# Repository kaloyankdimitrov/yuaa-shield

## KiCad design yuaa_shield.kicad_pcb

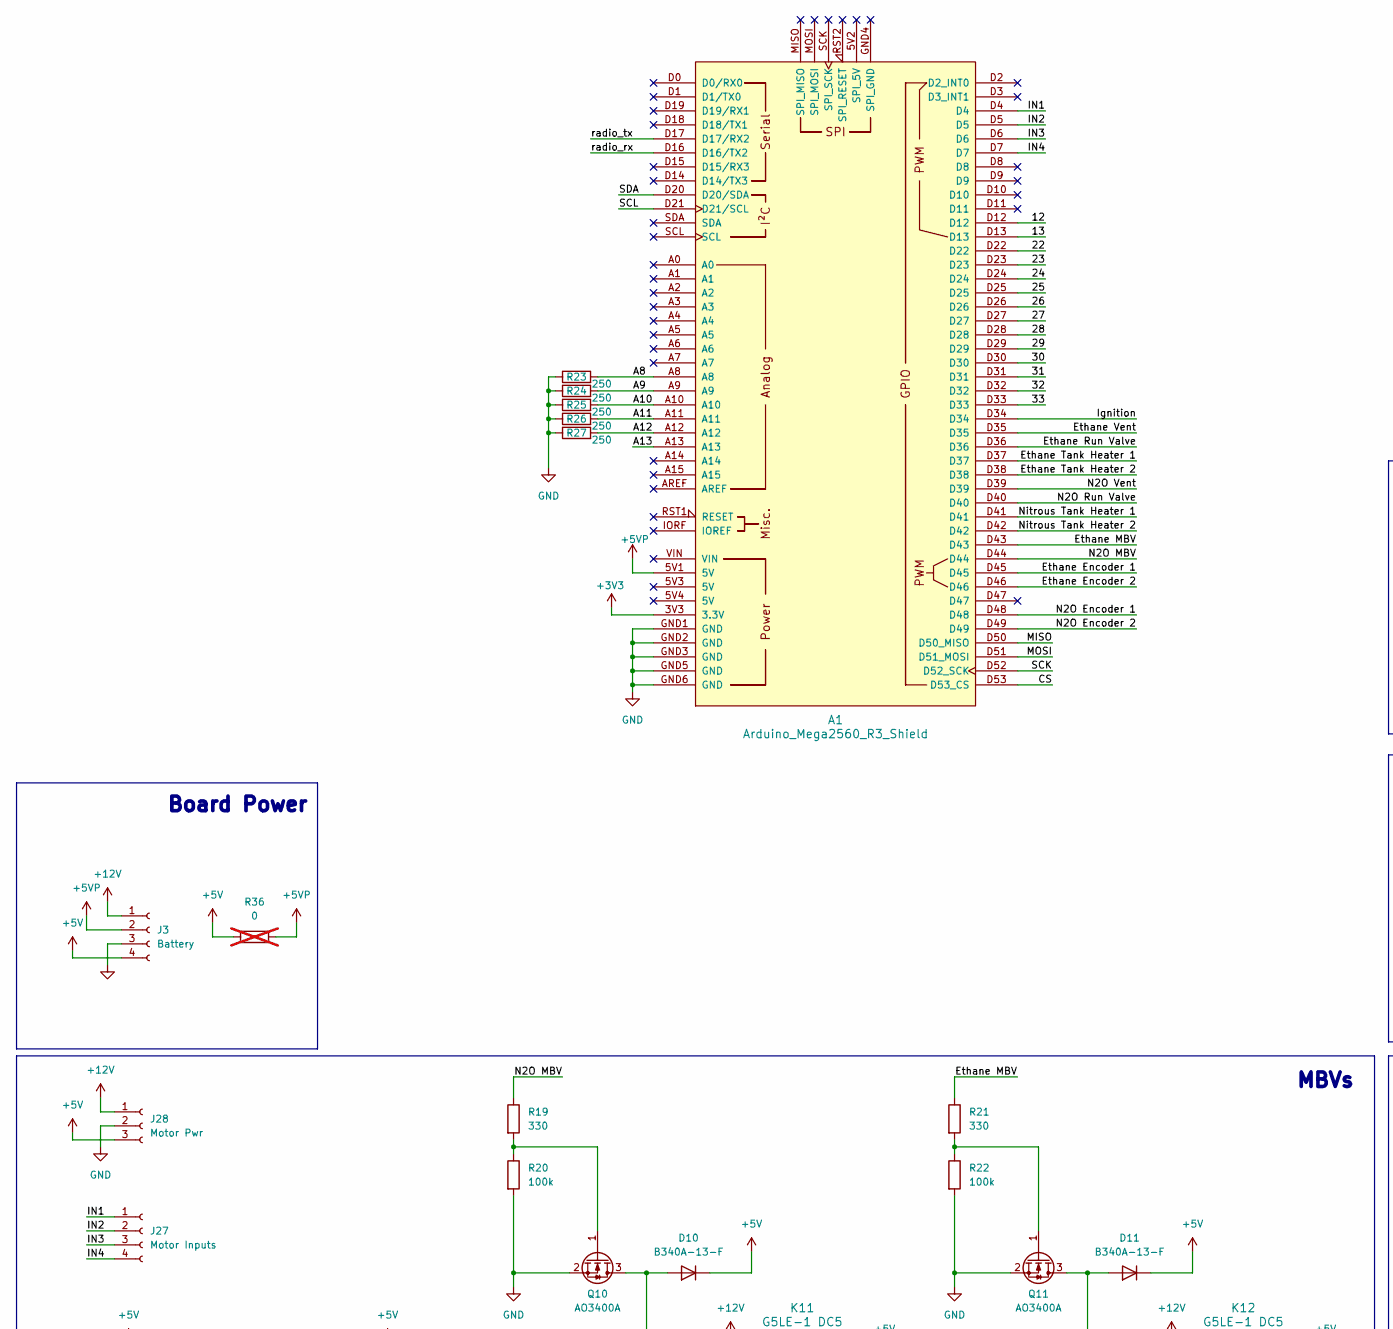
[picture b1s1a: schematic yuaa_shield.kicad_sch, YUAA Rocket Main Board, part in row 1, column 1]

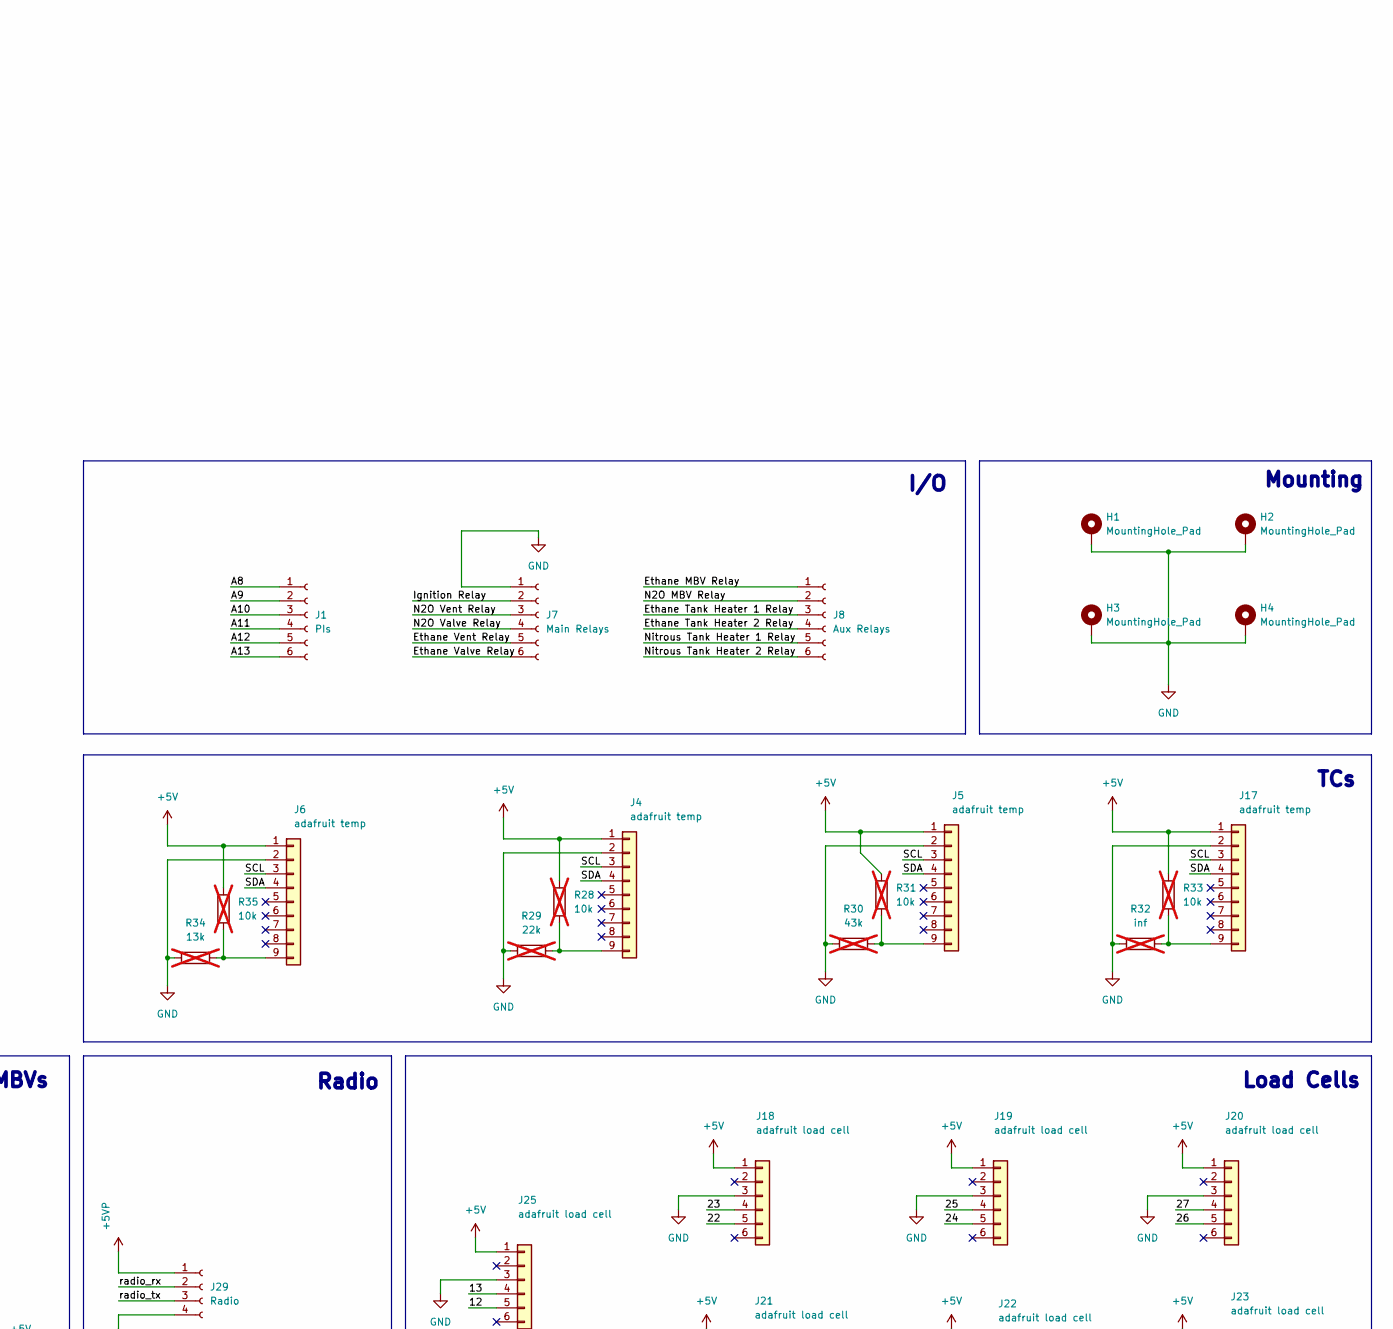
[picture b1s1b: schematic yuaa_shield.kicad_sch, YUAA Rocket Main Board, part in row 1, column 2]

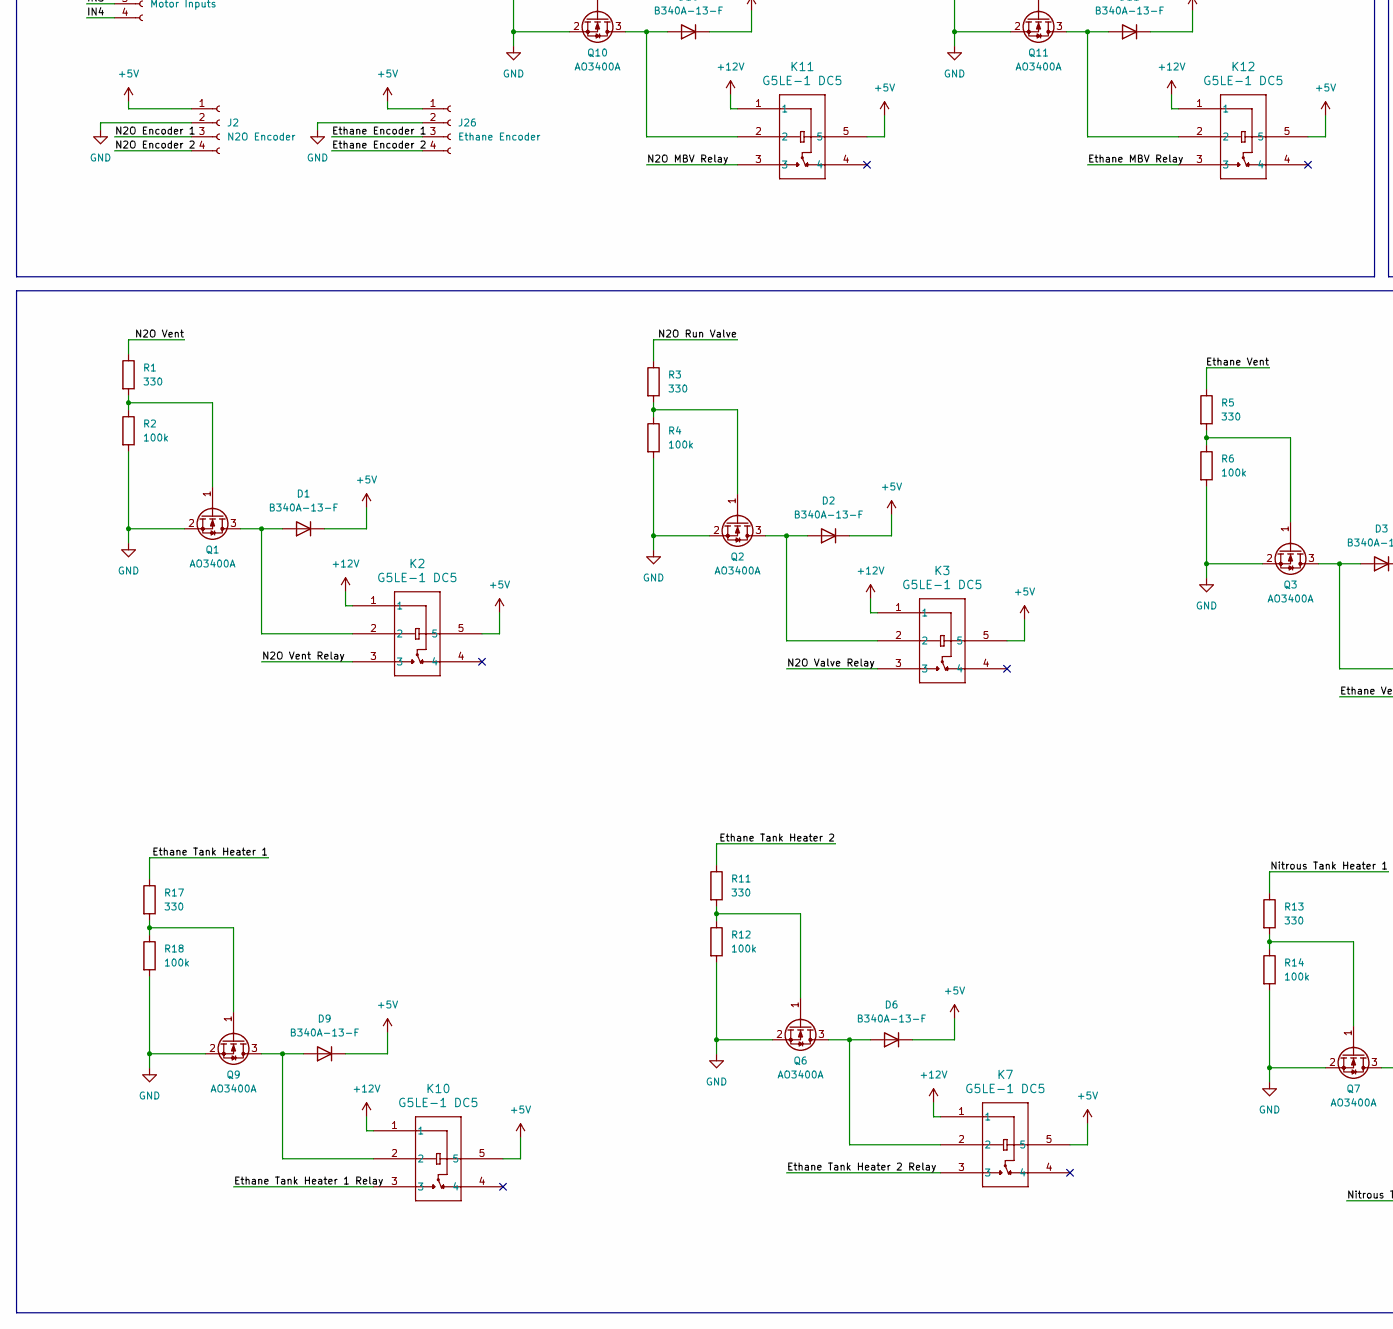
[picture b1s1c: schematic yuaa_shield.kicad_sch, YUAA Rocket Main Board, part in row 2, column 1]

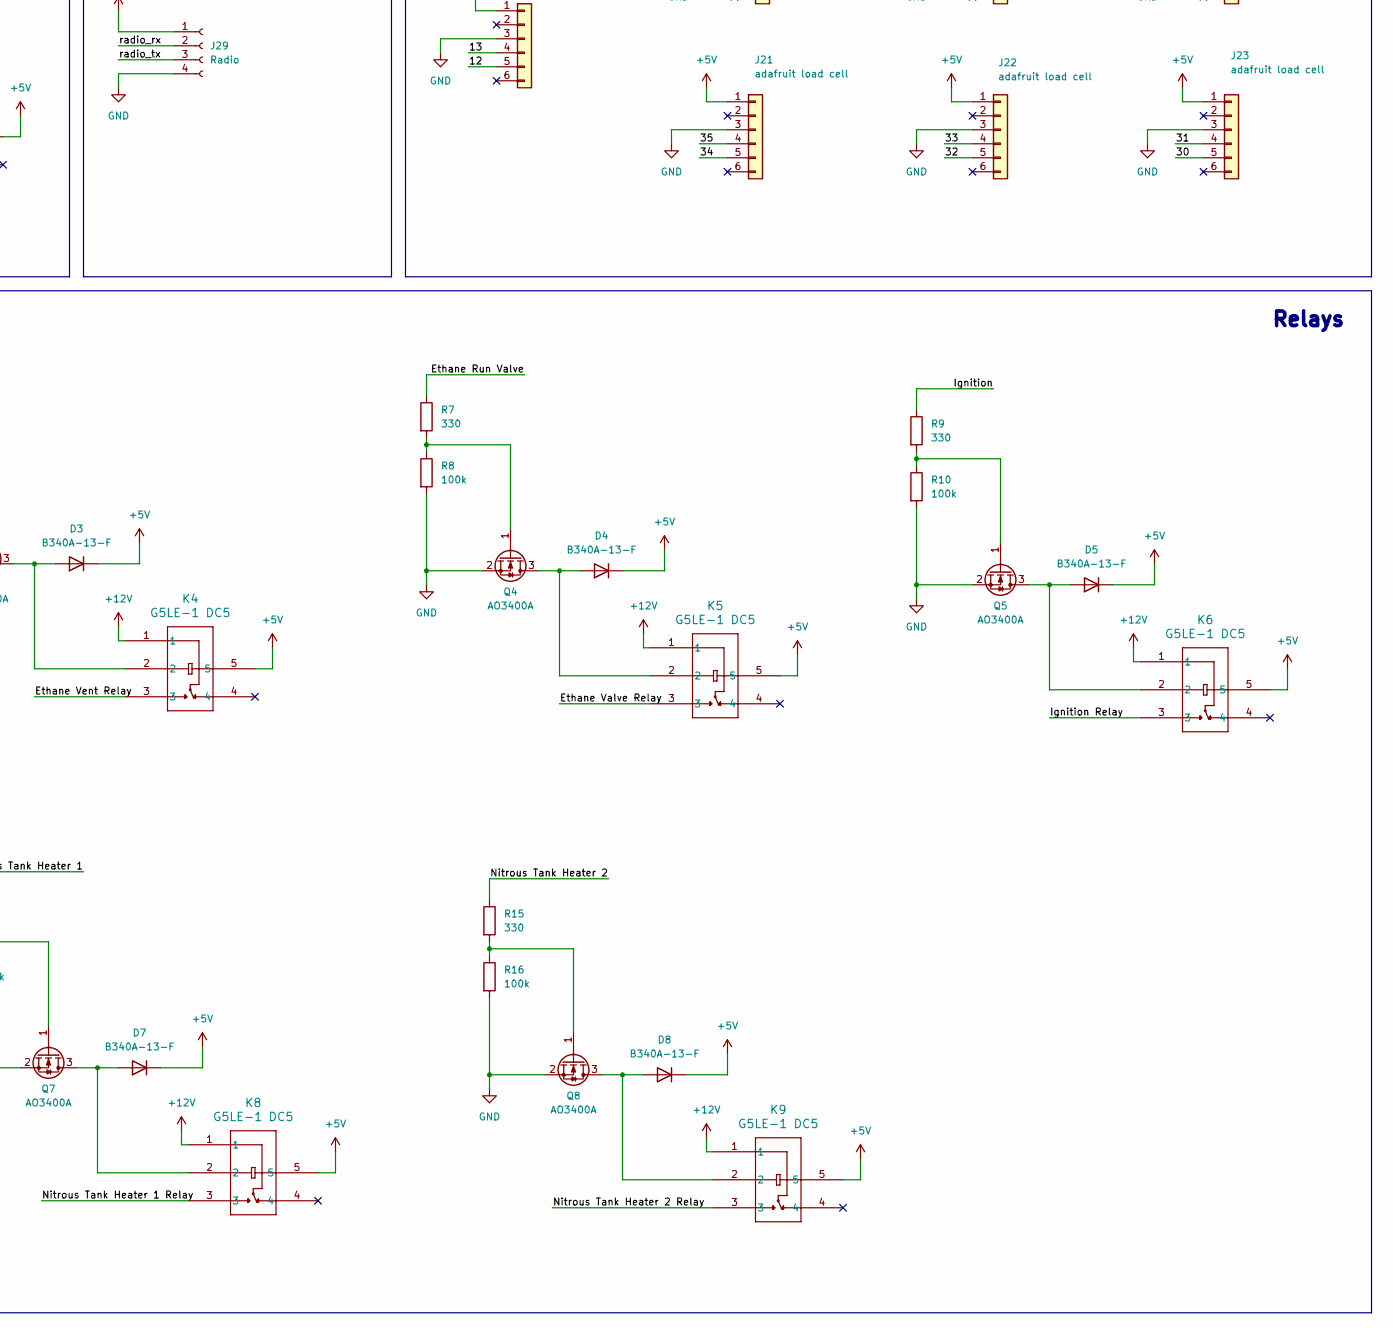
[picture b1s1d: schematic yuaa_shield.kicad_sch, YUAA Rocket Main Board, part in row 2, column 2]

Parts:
A1: Arduino_Mega2560_R3_Shield
D1, D2, D3, D4, D5, D6, D7, D8, D9, D10, D11: B340A-13-F; DIODE_SODB340_2P92X4P6_DIO-L
H1, H2, H3, H4: MountingHole_Pad; MountingHole_3.2mm_M3_Pad
J1: PIs; CUI_TB002-500-06BE
J2: N2O Encoder; CUI_TB002-500-04BE
J3: Battery; CUI_TB002-500-04BE
J4, J5, J6, J17: adafruit temp; MCP9601
J7: Main Relays; CUI_TB002-500-06BE
J8: Aux Relays; CUI_TB002-500-06BE
J18, J19, J20, J21, J22, J23, J25: adafruit load cell; HX711
J26: Ethane Encoder; CUI_TB002-500-04BE
J27: Motor Inputs; CUI_TB002-500-04BE
J28: Motor Pwr; CUI_TB002-500-03BE
J29: Radio; CUI_TB002-500-04BE
K2, K3, K4, K5, K6, K7, K8, K9, K10, K11, K12: G5LE-1 DC5; Relay_SPDT_Omron-G5LE-1
Q1, Q2, Q3, Q4, Q5, Q6, Q7, Q8, Q9, Q10, Q11: AO3400A; SOT-23
R1, R3, R5, R7, R9, R11, R13, R15, R17, R19, R21: 330; R_1206_3216Metric
R2, R4, R6, R8, R10, R12, R14, R16, R18, R20, R22: 100k; R_1206_3216Metric
R23, R24, R25, R26, R27: 250; R_1206_3216Metric
R28, R31, R33, R35: 10k; R_1206_3216Metric; not fitted
R29: 22k; R_1206_3216Metric; not fitted
R30: 43k; R_1206_3216Metric; not fitted
R32: inf; R_1206_3216Metric; not fitted
R34: 13k; R_1206_3216Metric; not fitted
R36: 0; R_1206_3216Metric; not fitted

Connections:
+3V3: A1.3V3 (3.3V)
+5V: D1.1 (K), D2.1 (K), D3.1 (K), D4.1 (K), D5.1 (K), D6.1 (K), D7.1 (K), D8.1 (K), D9.1 (K), D10.1 (K), D11.1 (K), J2.1, J3.4, J4.1, J5.1, J6.1, J17.1, J18.1, J19.1, J20.1, J21.1, J22.1, J23.1, J25.1, J26.1, J28.3, K2.5, K3.5, K4.5, K5.5, K6.5, K7.5, K8.5, K9.5, K10.5, K11.5, K12.5, R28.1, R31.1, R33.1, R35.1, R36.1
+5VP: A1.5V1 (5V), J3.2, J29.1, R36.2
+12V: J3.1, J28.1, K2.1, K3.1, K4.1, K5.1, K6.1, K7.1, K8.1, K9.1, K10.1, K11.1, K12.1
/12: A1.D12, J25.5
/13: A1.D13, J25.4
/22: A1.D22, J18.5
/23: A1.D23, J18.4
/24: A1.D24, J19.5
/25: A1.D25, J19.4
/26: A1.D26, J20.5
/27: A1.D27, J20.4
/28: A1.D28
/29: A1.D29
/30: A1.D30, J23.5
/31: A1.D31, J23.4
/32: A1.D32, J22.5
/33: A1.D33, J22.4
/34: J21.5
/35: J21.4
/A8: A1.A8, J1.1, R23.2
/A9: A1.A9, J1.2, R24.2
/A10: A1.A10, J1.3, R25.2
/A11: A1.A11, J1.4, R26.2
/A12: A1.A12, J1.5, R27.2
/A13: A1.A13, J1.6
/CS: A1.D53 (D53_CS)
/Ethane Encoder 1: A1.D45, J26.3
/Ethane Encoder 2: A1.D46, J26.4
/Ethane MBV: A1.D43, R21.1
/Ethane MBV Relay: J8.1, K12.3
/Ethane Run Valve: A1.D36, R7.1
/Ethane Tank Heater 1: A1.D37, R17.1
/Ethane Tank Heater 1 Relay: J8.3, K10.3
/Ethane Tank Heater 2: A1.D38, R11.1
/Ethane Tank Heater 2 Relay: J8.4, K7.3
/Ethane Valve Relay: J7.6, K5.3
/Ethane Vent: A1.D35, R5.1
/Ethane Vent Relay: J7.5, K4.3
/IN1: A1.D4, J27.1
/IN2: A1.D5, J27.2
/IN3: A1.D6, J27.3
/IN4: A1.D7, J27.4
/Ignition: A1.D34, R9.1
/Ignition Relay: J7.2, K6.3
/MISO: A1.D50 (D50_MISO)
/MOSI: A1.D51 (D51_MOSI)
/N2O Encoder 1: A1.D48, J2.3
/N2O Encoder 2: A1.D49, J2.4
/N2O MBV: A1.D44, R19.1
/N2O MBV Relay: J8.2, K11.3
/N2O Run Valve: A1.D40, R3.1
/N2O Valve Relay: J7.4, K3.3
/N2O Vent: A1.D39, R1.1
/N2O Vent Relay: J7.3, K2.3
/Nitrous Tank Heater 1: A1.D41, R13.1
/Nitrous Tank Heater 1 Relay: J8.5, K8.3
/Nitrous Tank Heater 2: A1.D42, R15.1
/Nitrous Tank Heater 2 Relay: J8.6, K9.3
/SCK: A1.D52 (D52_SCK)
/SCL: A1.D21 (D21/SCL), J4.3, J5.3, J6.3, J17.3
/SDA: A1.D20 (D20/SDA), J4.4, J5.4, J6.4, J17.4
/radio_rx: A1.D16 (D16/TX2), J29.2
/radio_tx: A1.D17 (D17/RX2), J29.3
GND: A1.GND1 (GND), A1.GND2 (GND), A1.GND3 (GND), A1.GND5 (GND), A1.GND6 (GND), H1.1 (1_1), H2.1 (1_1), H3.1 (1_1), H4.1 (1_1), J2.2, J3.3, J4.2, J5.2, J6.2, J7.1, J17.2, J18.3, J19.3, J20.3, J21.3, J22.3, J23.3, J25.3, J26.2, J28.2, J29.4, Q1.2 (S), Q2.2 (S), Q3.2 (S), Q4.2 (S), Q5.2 (S), Q6.2 (S), Q7.2 (S), Q8.2 (S), Q9.2 (S), Q10.2 (S), Q11.2 (S), R2.2, R4.2, R6.2, R8.2, R10.2, R12.2, R14.2, R16.2, R18.2, R20.2, R22.2, R23.1, R24.1, R25.1, R26.1, R27.1, R29.1, R30.1, R32.1, R34.1
unnamed: D1.2 (A), K2.2, Q1.3 (D)
unnamed: D2.2 (A), K3.2, Q2.3 (D)
unnamed: D3.2 (A), K4.2, Q3.3 (D)
unnamed: D4.2 (A), K5.2, Q4.3 (D)
unnamed: D5.2 (A), K6.2, Q5.3 (D)
unnamed: D6.2 (A), K7.2, Q6.3 (D)
unnamed: D7.2 (A), K8.2, Q7.3 (D)
unnamed: D8.2 (A), K9.2, Q8.3 (D)
unnamed: D9.2 (A), K10.2, Q9.3 (D)
unnamed: D10.2 (A), K11.2, Q10.3 (D)
unnamed: D11.2 (A), K12.2, Q11.3 (D)
unnamed: J4.9, R28.2, R29.2
unnamed: J5.9, R30.2, R31.2
unnamed: J6.9, R34.2, R35.2
unnamed: J17.9, R32.2, R33.2
unnamed: Q1.1 (G), R1.2, R2.1
unnamed: Q2.1 (G), R3.2, R4.1
unnamed: Q3.1 (G), R5.2, R6.1
unnamed: Q4.1 (G), R7.2, R8.1
unnamed: Q5.1 (G), R9.2, R10.1
unnamed: Q6.1 (G), R11.2, R12.1
unnamed: Q7.1 (G), R13.2, R14.1
unnamed: Q8.1 (G), R15.2, R16.1
unnamed: Q9.1 (G), R17.2, R18.1
unnamed: Q10.1 (G), R19.2, R20.1
unnamed: Q11.1 (G), R21.2, R22.1

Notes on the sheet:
Load Cells
Relays
I/O
Radio
Mounting
Board Power
TCs
MBVs

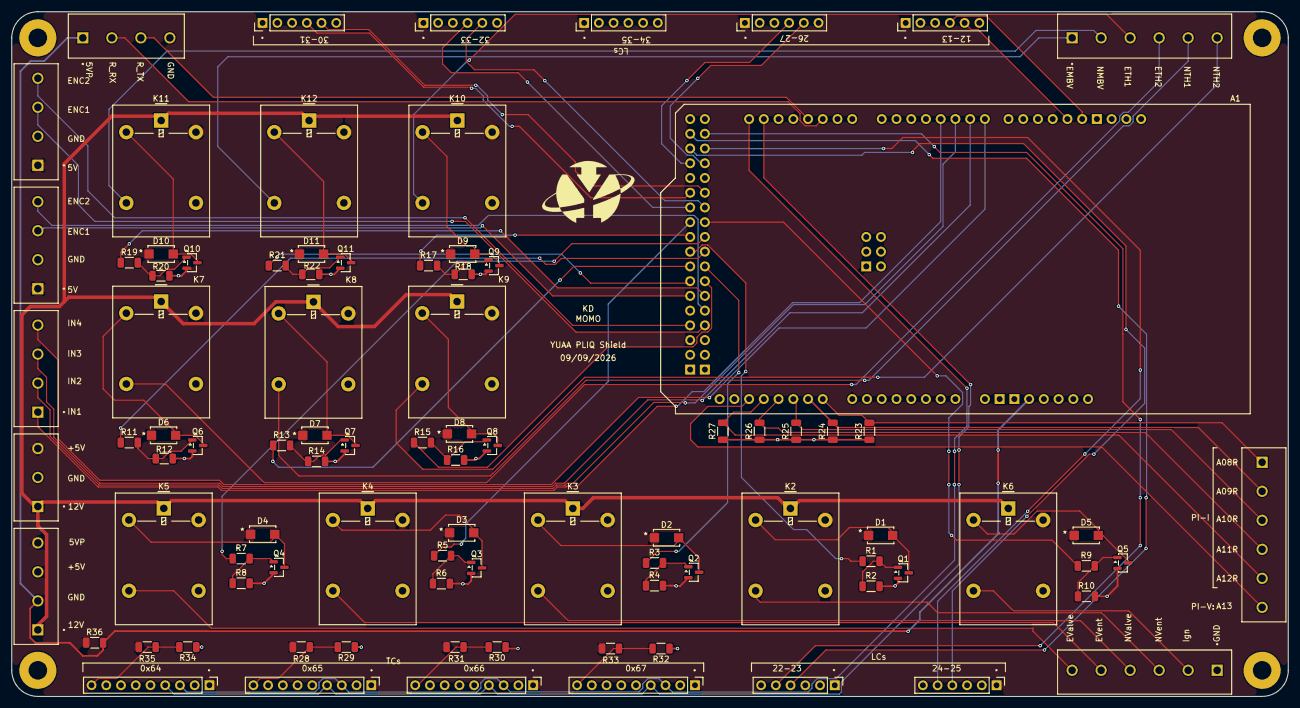
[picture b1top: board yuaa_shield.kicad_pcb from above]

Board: 2 copper layers, 220.0 x 118.0 mm, 94 parts (0 on the bottom side), 82 nets.

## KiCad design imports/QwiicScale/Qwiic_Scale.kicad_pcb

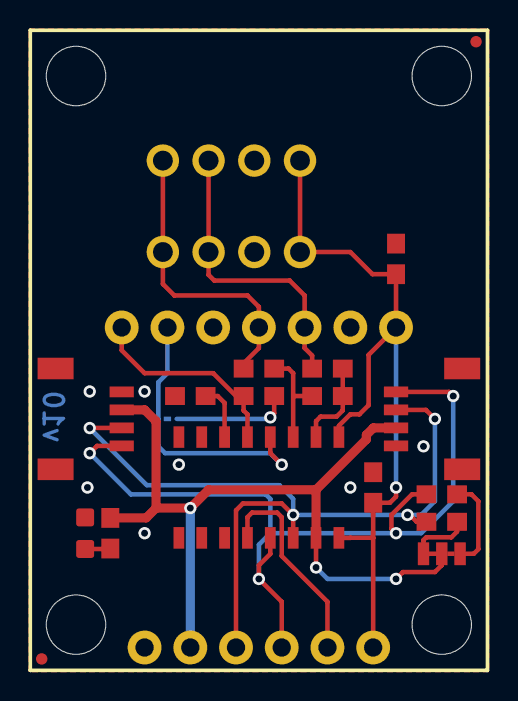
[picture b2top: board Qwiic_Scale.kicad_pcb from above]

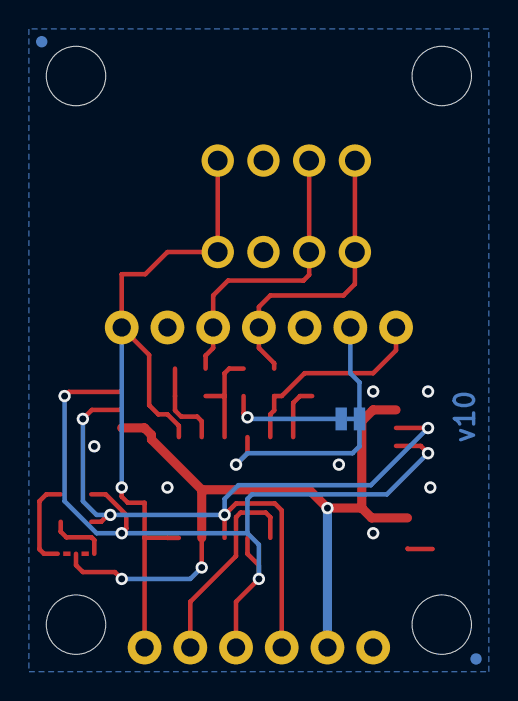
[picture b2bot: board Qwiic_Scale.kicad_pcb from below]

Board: 2 copper layers, 68 parts (26 on the bottom side), 17 nets.

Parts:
C8, C9, C10: 0.1uF; 0603
C11: 330pF; 0603
C12: 1.0uF; 0603
D1: RED; LED-0603
FRAME1: FRAME-LETTER; CREATIVE_COMMONS
J1: CAP; SMT-JUMPER_2_NC_TRACE_SILK
J2, J4: Qwiic Right Angle; JST04_1MM_RA
J3: PTH; 1X04_NO_SILK
J5: 1X02_NO_SILK
J7: Spring Terminal; 1X04_SPRING_TERMINAL
JP1: 1X05_NO_SILK
JP2: 1X02_NO_SILK
JP3: I2C; SMT-JUMPER_3_2-NC_TRACE_SILK
JP21, JP61, JP71, JP81: FIDUCIALUFIDUCIAL; MICRO-FIDUCIAL
JP31, JP41, JP91, JP101: STAND-OFF
LOGO1: OSHW-LOGOMINI; OSHW-LOGO-MINI
LOGO2, LOGO3: SFE_LOGO_NAME_FLAME.1_INCH; SFE_LOGO_NAME_FLAME_.1
R1: 1k; 0603
R2, R3: 2.2k; 0603
R9, R10: 47; 0603
U1: NAU7802; SO16
U$1, U$4: SDA-[)
U$3, U$5: SCL-[)
U$6, U$7: 3V3-04
U$8, U$9: GND-04
U$11: YLW#SD4
U$12: B#11
U$13: B#12
U$14, U$22: QWIIC2
U$15, U$21: INT0
U$17, U$24: SCALE3
U$18: PWR-()-03
U$19: I_SUPER2_C-()-03
U$20: CAP0
U$26: QWIIC_LOGO_8MM; QWIIC_8MM
U$34: BLK#E#1
U$35: GRN#A#4
U$36, U$45: AVDD4
U$37: BLACK5
U$38: BLK1
U$39: GREEN7
U$40: GRN3
U$41: RED0
U$42: RED4
U$43: WHITE6
U$44: WHT2
U$46: RED#E#2
U$48: WHT#A#3

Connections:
3.3V: J2.2, J3.2, J4.2, JP3.2, R1.2, U1.15
A+: J7.4, J7.8, JP1.2, R10.1
A-: J7.3, J7.7, JP1.3, R9.1
B+: C11.2, JP2.1, U1.5
B-: J1.2, JP2.2, U1.4
GND: C9.2, C10.2, C12.2, D1.C, J2.1, J3.1, J4.1, J7.2, J7.6, JP1.1, JP1.4, U1.7, U1.8, U1.9
INT: J5.2, U1.12
unnamed: C11.1, J1.1
unnamed: JP3.1, R3.2
unnamed: JP3.3, R2.2
unnamed: D1.A, R1.1
unnamed: C10.1, U1.6
unnamed: C8.2, R10.2, U1.3
unnamed: C8.1, R9.2, U1.2
SCL: J2.4, J3.4, J4.4, R2.1, U1.13
SDA: J2.3, J3.3, J4.3, R3.1, U1.14
VDDA: C9.1, C12.1, J5.1, J7.1, J7.5, JP1.5, U1.1, U1.16

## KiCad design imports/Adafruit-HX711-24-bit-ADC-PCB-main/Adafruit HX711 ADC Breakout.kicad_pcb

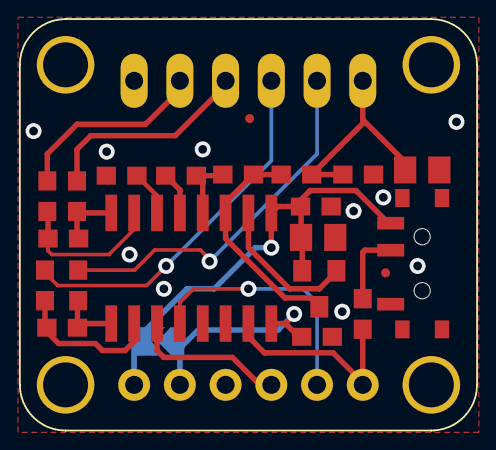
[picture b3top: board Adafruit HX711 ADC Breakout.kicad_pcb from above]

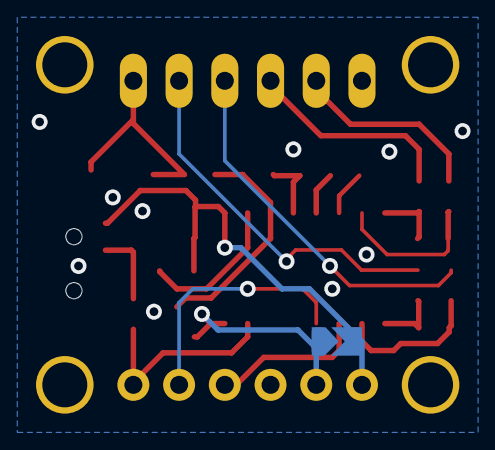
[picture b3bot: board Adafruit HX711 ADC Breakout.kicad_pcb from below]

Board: 2 copper layers, 55 parts (11 on the bottom side), 20 nets.

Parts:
C1, C2, C5, C7, C8, C9: 0.1uF; 0603-NO
C3, C4: 10uF; 0805-NO
FID3, FID4: FIDUCIAL_0.5MM
JP1: 1X06_ROUND_70
JP2: 6pin 2.54mm; 1X06_2.54MMTERMINAL
L1: 3.3uH MLF1608A3R3JT000; 0603-NO
PLABEL0: PLABEL0
PLABEL1: PLABEL1
PLABEL2: PLABEL2
PLABEL3: PLABEL3
PLABEL4: PLABEL4
PLABEL5: PLABEL5
PLABEL6: PLABEL6
PLABEL7: PLABEL7
PLABEL8: PLABEL8
PLABEL9: PLABEL9
PLABEL10: PLABEL10
PLABEL11: PLABEL11
PLABEL12: PLABEL12
PLABEL13: PLABEL13
PLABEL14: PLABEL14
PLABEL15: PLABEL15
PLABEL16: PLABEL16
PLABEL17: PLABEL17
PLABEL18: PLABEL18
PLABEL19: PLABEL19
PLABEL20: PLABEL20
PLABEL21: PLABEL21
PLABEL22: PLABEL22
PLABEL23: PLABEL23
Q1: S8550; SOT23-WIDE
R1, R2, R4, R5: 100; 0603-NO
R6: 8.2K; 0603-NO
R7: 20K; 0603-NO
R8: 10K; 0603-NO
SJ1: SOLDERJUMPER_ARROW_NOPASTE
SW1: SPDT; SPDT_SMT_SSSS811101
U$1, U$17, U$19, U$21: MOUNTINGHOLE2.5; MOUNTINGHOLE_2.5_PLATED
U$11: ADAFRUIT_2.5MM
U$22: ADAFRUIT_3.5MM
U$25: PCBFEAT-REV-040
X3: HX711; SO16

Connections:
A+: JP2.4, R2.2
A-: JP2.5, R1.2
AVDD: L1.1, Q1.3, R7.2, X3.3
B+: JP2.3, R5.2
B-: JP2.2, R4.2
BASE: Q1.1, X3.2
DATAOUT: JP1.5, X3.12
GND: C1.2, C2.2, C3.2, C4.2, C5.2, C8.1, JP1.3, JP2.6, R6.2, SW1.A, X3.5, X3.14
unnamed: R8.2, SW1.B
unnamed: C7.1, R2.1, X3.8
unnamed: C7.2, R1.1, X3.7
unnamed: C9.1, R5.1, X3.10
unnamed: C9.2, R4.1, X3.9
RATE: JP1.6, R8.1, X3.15
SCLK: JP1.4, X3.11
V+: C1.1, C3.1, JP1.1, Q1.2, SJ1.2, SW1.C, X3.1
VBG: C8.2, X3.6
VDDIO: C2.1, JP1.2, SJ1.1, X3.16
VFB: R6.1, R7.1, X3.4
VPP: C4.1, C5.1, JP2.1, L1.2
